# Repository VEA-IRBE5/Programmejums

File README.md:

# Programmējums
Zondes borta datora (mikrokontroliera) programmējums

# Programmēšanas stila vadlīnijas
Šīs ir tikai vadlīnijas, nesitīšu ja perfekti nesekosiet tām. Galvenais, lai kods ir saprotams un pārskatāms
- Tabulācija ir 4 atstarpes
- Komentārus var latviski/english, galvenais lai ir saprotami un labi apraksta kodu
- Iesaku komentārus netaupīt, tiklīdz kaut kas liekas ne pilnīgi pašsaprotams, raksti komentāru
- Komentāru garumam nevajadzētu pārsniegt 2 - 3 līnijas

## Mainīgo noformējums

- Mainīgo nosaukums var būt īsi līdz vidēji tekstuāls, galvenais lai no nosaukuma ir aptuveni skaidrs, kur izmanto
- Visim mainīgiem ir jābūt definētiem vienā vietā (vai divās) un, kur nepieiciešams, ar komentāriem aprakstīts to pielietojums
- Šīs pašas vadlīnijas arī attiecas uz definētām konstantēm
- Lūgums turēt mainīgos ārpus header (main.h) faila, cik iespējams (Uz konstantēm tas neattiecas)

## Koda noformējums

- Galvenā doma ir sadalīšana pa blokiem ar attiecīgām komentētām sadalēm
- Piemērā ir redzams ADC pārtraukums kā galvenais bloks, ar iekšējiem darbības soļiem sadalītiem mazākos blokos
- Var dalīt kodu pa blokiem arī pēc saviem ieskatiem, galvenais lai ir labi sadalīts

## #include un funkcijas

- Pie #include droši rakstiet komentārus
- Funkcijām lūdzu veidot aprakstu, pasakot ko dara, ko ievada (ar mainīgo aprakstu) un ko izvada
- Ja izmantojat gatavus koda blokus no citiem avotiem, tos iesaku turēt atsevišķos failos un integrēt kā funkcijas

# Git bash konfigurācija un lokālās repozitorijas izveide

### 1. Instalē git bash

### 2. Izveido mapi, kurā glabās projektu

### 3. R-click(otrais peles taustiņš) -> Git bash here
  - Ja nerāda, atver git bash un ar cd navigē uz izveidoto mapi

### 4. Konsolē: git config --global user.name "Vards Uzvards" 
- git config --global user.email "epasts@mail.com"
  - Izmanto to epastu, kurš piesaistīts profilam, kas var tikt klāt IRBE5 repozitorijai
  - Var pārbaudīt, vai pareizi saglabāts ar tām pašām komandām, noņemot "" specificētos datus

### 5. (Neobligāts)Konsolē: git config --global core.editor "'C:/Program Files/Notepad++/notepad++.exe' -multiInst -notabbar -nosession -noPlugin"
  - var uzstādīt notepad++ kā default teksta editoru, kad raksta commit komentāru
  - Iesaku izdarīt, jo konsoles teksta editors nav ērts

### 6. Konsolē: git config --global init.defaultBranch main
- Citādi defaults būs master, un tas var radīt problēmas

### 7. Konsolē: git config --list
- Ar šo var pārbaudīt git bash konfigurāciju

### 8. Beidzot inicializē lokālo repozitoriju: git init

# Darbība ar lokālo github repositoriju

### 1. Konsolē: git remote add IRBE5 https://github.com/VEA-IRBE5/Programmejums.git
- turpmāk pie git pull var izmantot IRBE5 nevis pilno linku 
- ar šo pastās, vai sarakstā ir Konsolē: git remote -v

### 2. Konsolē: git pull IRBE5 [Branch name]
- Lejupielādē norādītā zara saturu no repozitorijas, par zaru lietošanu konsultējies ar nodaļas galveno

### 3. Pēc pašreizējās darba tūres beigšanas neaizmirsti izveidot commit, lai dati nepazūd
- Konsolē: git add . (vai git add "filename", ja negrib visas izmaiņas pievienot)
- Konsolē: git status (pastās, vai viss ir ok)
- Konsolē: git commit (Lūdzu izsmeļoši un ne pārāk gari aprakstiet izmainīto)(var izmantot: -m "Text here")
   
### 4. Kad liekas, ka pašreizējais uzdevums ir gana labā stāvoklī, Konsolē: git push IRBE5 [Branch name]

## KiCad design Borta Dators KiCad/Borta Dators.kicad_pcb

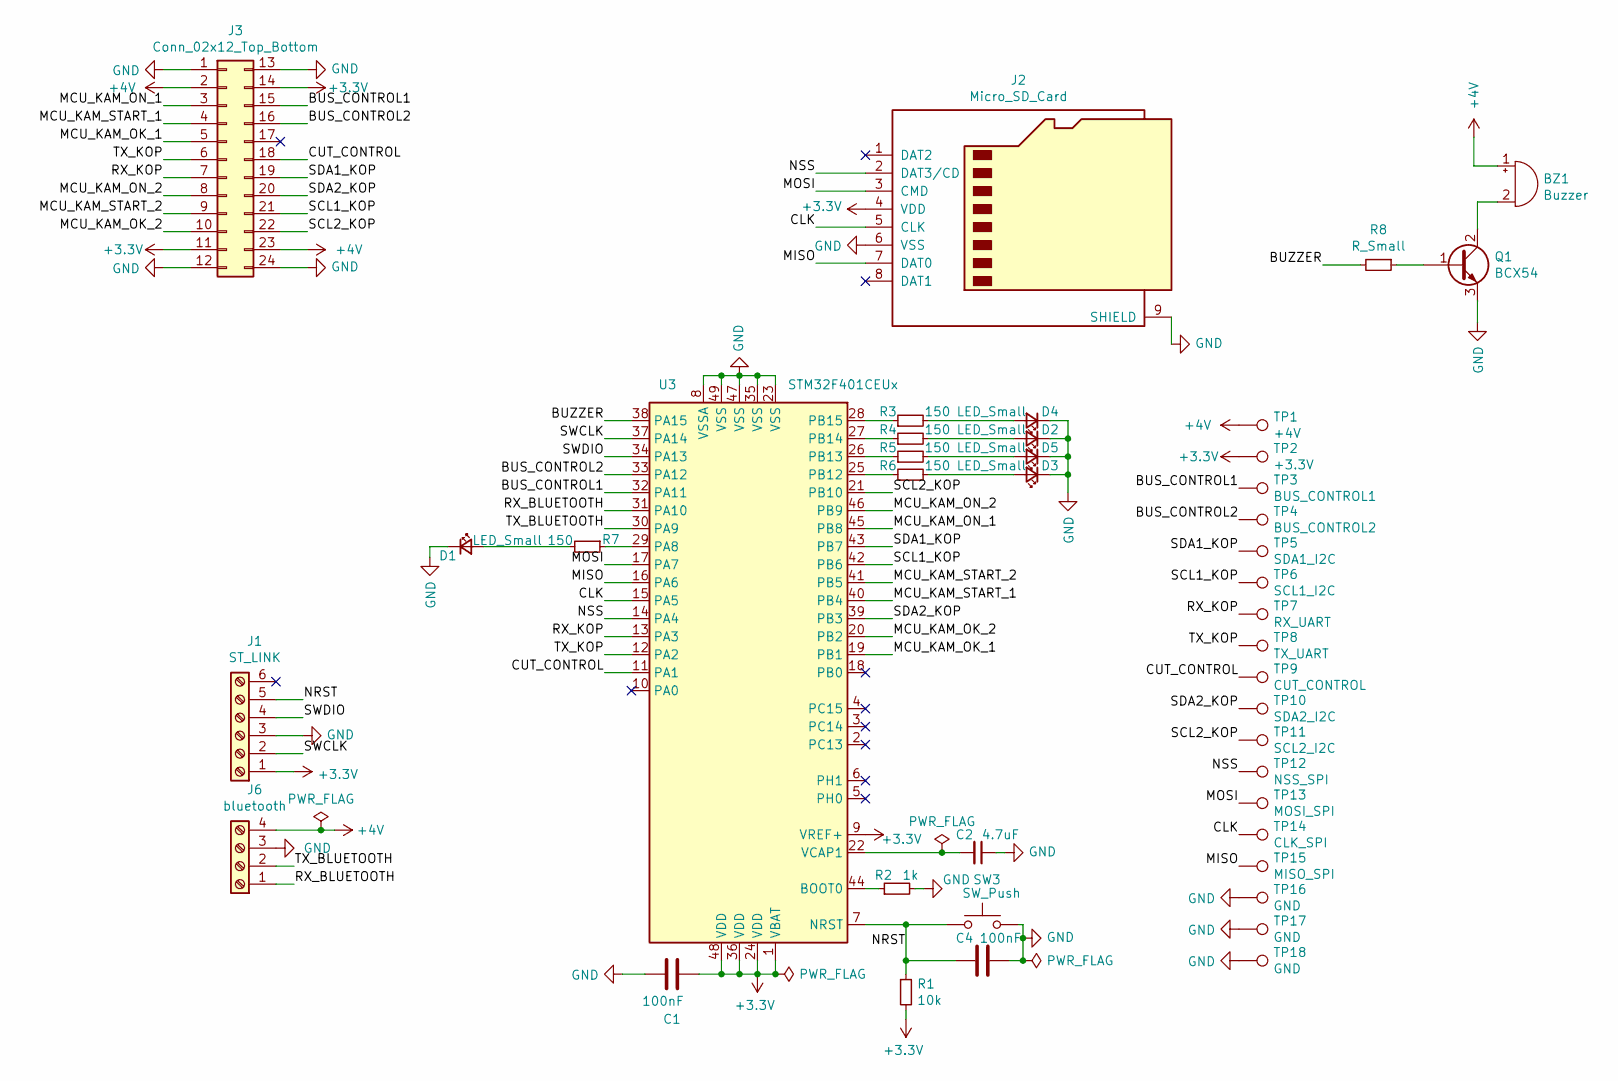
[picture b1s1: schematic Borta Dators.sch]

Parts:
BZ1: Buzzer; PinHeader_1x02_P1.27mm_Vertical
C1, C4: 100nF; C_0603_1608Metric_Pad1.08x0.95mm_HandSolder
C2: 4.7uF; C_0603_1608Metric_Pad1.08x0.95mm_HandSolder
D1, D2, D3, D4, D5: LED_Small; D_0603_1608Metric_Pad1.05x0.95mm_HandSolder
J1: ST_LINK; PinSocket_1x06_P2.54mm_Vertical
J2: Micro_SD_Card; Micro_SD
J3: Conn_02x12_Top_Bottom; SAMTEC-SSW-112-02-X-D-RA
J6: bluetooth; PinSocket_1x04_P2.54mm_Vertical
Q1: BCX54; SOT-89-3
R1: 10k; R_0603_1608Metric_Pad0.98x0.95mm_HandSolder
R2: 1k; R_0603_1608Metric_Pad0.98x0.95mm_HandSolder
R3, R4, R5, R6, R7: 150; R_0603_1608Metric_Pad0.98x0.95mm_HandSolder
R8: R_Small; R_0603_1608Metric_Pad0.98x0.95mm_HandSolder
SW3: SW_Push; SW_SPST_EVQQ2
TP1: +4V; PinHeader_1x01_P2.54mm_Vertical
TP2: +3.3V; PinHeader_1x01_P2.54mm_Vertical
TP3: BUS_CONTROL1; PinHeader_1x01_P2.54mm_Vertical
TP4: BUS_CONTROL2; PinHeader_1x01_P2.54mm_Vertical
TP5: SDA1_I2C; PinHeader_1x01_P2.54mm_Vertical
TP6: SCL1_I2C; PinHeader_1x01_P2.54mm_Vertical
TP7: RX_UART; PinHeader_1x01_P2.54mm_Vertical
TP8: TX_UART; PinHeader_1x01_P2.54mm_Vertical
TP9: CUT_CONTROL; PinHeader_1x01_P2.54mm_Vertical
TP10: SDA2_I2C; PinHeader_1x01_P2.54mm_Vertical
TP11: SCL2_I2C; PinHeader_1x01_P2.54mm_Vertical
TP12: NSS_SPI; PinHeader_1x01_P2.54mm_Vertical
TP13: MOSI_SPI; PinHeader_1x01_P2.54mm_Vertical
TP14: CLK_SPI; PinHeader_1x01_P2.54mm_Vertical
TP15: MISO_SPI; PinHeader_1x01_P2.54mm_Vertical
TP16, TP17, TP18: GND; PinHeader_1x01_P2.54mm_Vertical
U3: STM32F401CEUx; QFN-48-1EP_7x7mm_P0.5mm_EP5.6x5.6mm

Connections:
+3V3: C1.1, J1.1, J2.4 (VDD), J3.11, J3.14, R1.2, TP2.1, U3.1 (VBAT), U3.9 (VREF+), U3.24 (VDD), U3.36 (VDD), U3.48 (VDD); also elsewhere on the board
+4V: BZ1.1 (-), J3.2, J3.23, J6.4, TP1.1
/BUS_CONTROL1: J3.15, TP3.1, U3.32 (PA11); also elsewhere on the board
/BUS_CONTROL2: J3.16, TP4.1, U3.33 (PA12); also elsewhere on the board
/BUZZER: R8.2, U3.38 (PA15); also elsewhere on the board
/CLK: J2.5 (CLK), TP14.1, U3.15 (PA5); also elsewhere on the board
/CUT_CONTROL: J3.18, TP9.1, U3.11 (PA1); also elsewhere on the board
/MCU_KAM_OK_1: J3.5, U3.19 (PB1); also elsewhere on the board
/MCU_KAM_OK_2: J3.10, U3.20 (PB2); also elsewhere on the board
/MCU_KAM_ON_1: J3.3, U3.45 (PB8); also elsewhere on the board
/MCU_KAM_ON_2: J3.8, U3.46 (PB9); also elsewhere on the board
/MCU_KAM_START_1: J3.4, U3.40 (PB4); also elsewhere on the board
/MCU_KAM_START_2: J3.9, U3.41 (PB5); also elsewhere on the board
/MISO: J2.7 (DAT0), TP15.1, U3.16 (PA6); also elsewhere on the board
/MOSI: J2.3 (CMD), TP13.1, U3.17 (PA7); also elsewhere on the board
/NRST: C4.1, J1.5, R1.1, SW3.1, U3.7 (NRST); also elsewhere on the board
/NSS: J2.2 (DAT3/CD), TP12.1, U3.14 (PA4); also elsewhere on the board
/RX_BLUETOOTH: J6.1, U3.31 (PA10); also elsewhere on the board
/RX_KOP: J3.7, TP7.1, U3.13 (PA3); also elsewhere on the board
/SCL1_KOP: J3.21, TP6.1, U3.42 (PB6); also elsewhere on the board
/SCL2_KOP: J3.22, TP11.1, U3.21 (PB10); also elsewhere on the board
/SDA1_KOP: J3.19, TP5.1, U3.43 (PB7); also elsewhere on the board
/SDA2_KOP: J3.20, TP10.1, U3.39 (PB3); also elsewhere on the board
/SWCLK: J1.2, U3.37 (PA14); also elsewhere on the board
/SWDIO: J1.4, U3.34 (PA13); also elsewhere on the board
/TX_BLUETOOTH: J6.2, U3.30 (PA9); also elsewhere on the board
/TX_KOP: J3.6, TP8.1, U3.12 (PA2); also elsewhere on the board
GND: C1.2, C2.1, C4.2, D1.1 (K), D2.1 (K), D3.1 (K), D4.1 (K), D5.1 (K), J1.3, J2.6 (VSS), J2.9 (SHIELD), J3.1, J3.12, J3.13, J3.24, J6.3, Q1.3 (E), R2.2, SW3.2, TP16.1, TP17.1, TP18.1, U3.8 (VSSA), U3.23 (VSS), U3.35 (VSS), U3.47 (VSS), U3.49 (VSS); also elsewhere on the board
unnamed: BZ1.2 (+), Q1.2 (C)
unnamed 29: C2.2, U3.22 (VCAP1); also elsewhere on the board
unnamed: D1.2 (A), R7.2
unnamed: D2.2 (A), R4.2
unnamed: D3.2 (A), R6.2
unnamed: D4.2 (A), R3.2
unnamed: D5.2 (A), R5.2
unnamed: Q1.1 (B), R8.1
unnamed 40: R2.1, U3.44 (BOOT0); also elsewhere on the board
unnamed 41: R3.1, U3.28 (PB15); also elsewhere on the board
unnamed 42: R4.1, U3.27 (PB14); also elsewhere on the board
unnamed 43: R5.1, U3.26 (PB13); also elsewhere on the board
unnamed 44: R6.1, U3.25 (PB12); also elsewhere on the board
unnamed 45: R7.1, U3.29 (PA8); also elsewhere on the board

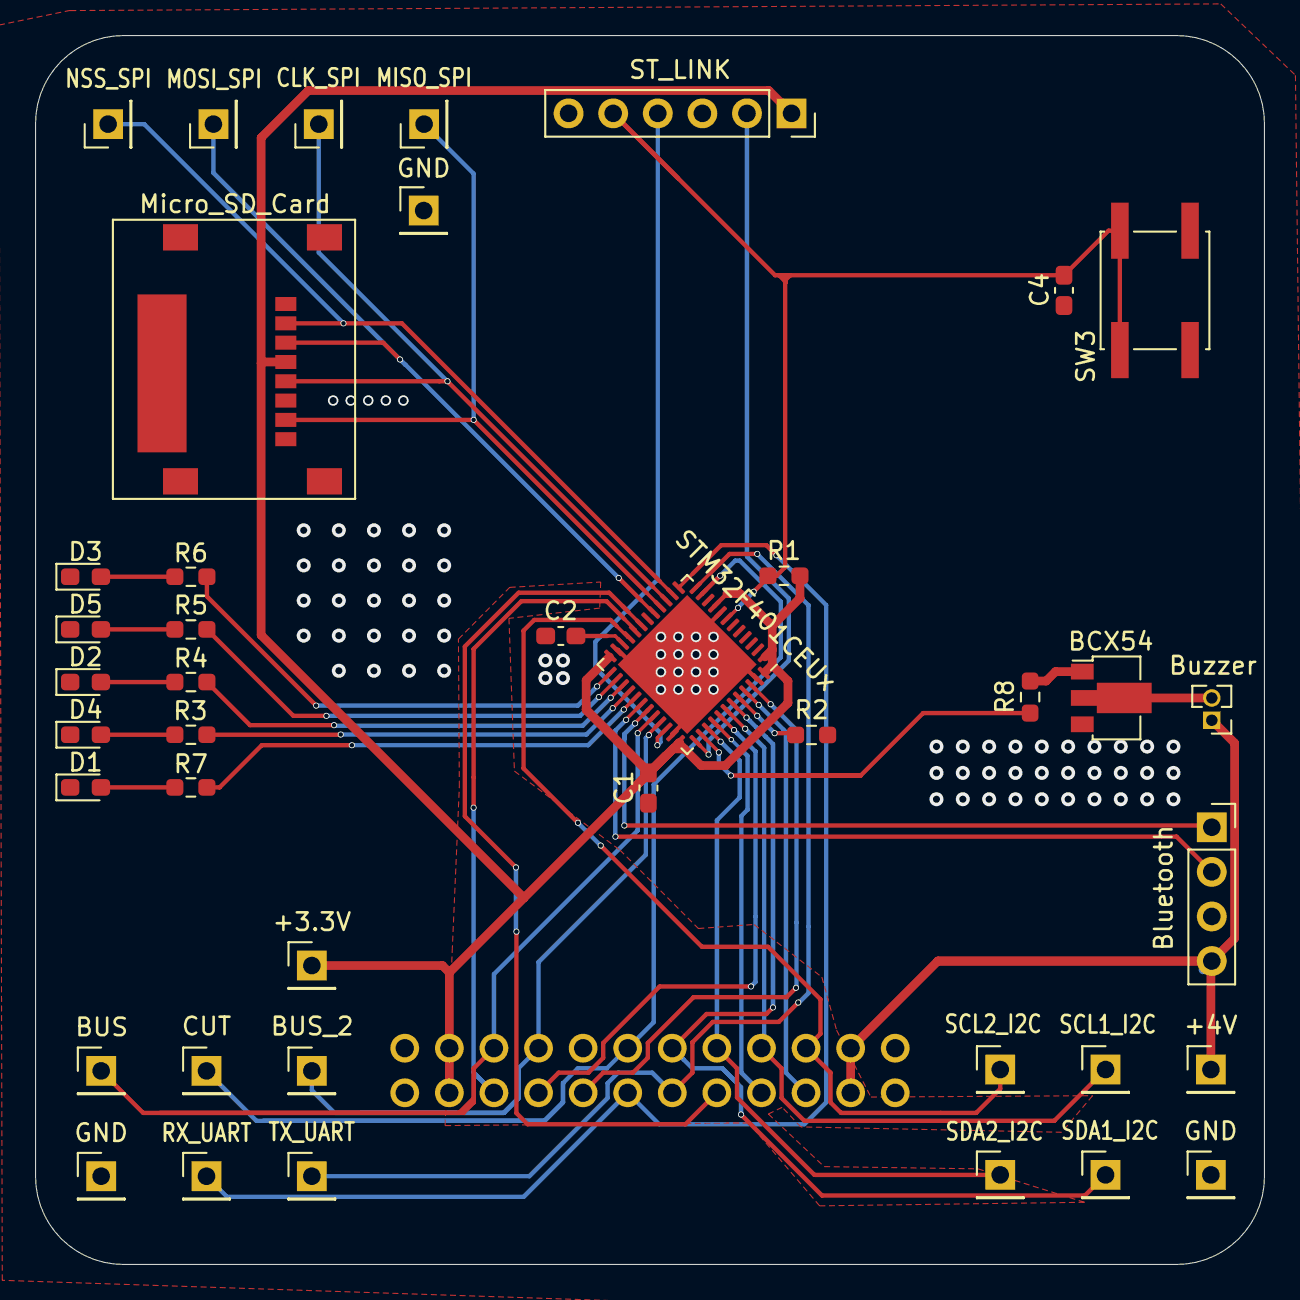
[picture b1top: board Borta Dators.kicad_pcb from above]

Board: 2 copper layers, 70.0 x 70.0 mm, 42 parts (0 on the bottom side), 42 nets.

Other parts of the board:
TP109: BUS_2; PinHeader_1x01_P2.54mm_Vertical
Ue: STM32F401CEUx; QFN-48-1EP_7x7mm_P0.5mm_EP5.6x5.6mm

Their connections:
+3V3: Ue.1, Ue.9, Ue.24, Ue.36, Ue.48; also elsewhere on the board
/BUS_CONTROL1: Ue.32; also elsewhere on the board
/BUS_CONTROL2: TP109.1, Ue.33; also elsewhere on the board
/BUZZER: Ue.38; also elsewhere on the board
/CLK: Ue.15; also elsewhere on the board
/CUT_CONTROL: Ue.11; also elsewhere on the board
/MCU_KAM_OK_1: Ue.19; also elsewhere on the board
/MCU_KAM_OK_2: Ue.20; also elsewhere on the board
/MCU_KAM_ON_1: Ue.45; also elsewhere on the board
/MCU_KAM_ON_2: Ue.46; also elsewhere on the board
/MCU_KAM_START_1: Ue.40; also elsewhere on the board
/MCU_KAM_START_2: Ue.41; also elsewhere on the board
/MISO: Ue.16; also elsewhere on the board
/MOSI: Ue.17; also elsewhere on the board
/NRST: Ue.7; also elsewhere on the board
/NSS: Ue.14; also elsewhere on the board
/RX_BLUETOOTH: Ue.31; also elsewhere on the board
/RX_KOP: Ue.13; also elsewhere on the board
/SCL1_KOP: Ue.42; also elsewhere on the board
/SCL2_KOP: Ue.21; also elsewhere on the board
/SDA1_KOP: Ue.43; also elsewhere on the board
/SDA2_KOP: Ue.39; also elsewhere on the board
/SWCLK: Ue.37; also elsewhere on the board
/SWDIO: Ue.34; also elsewhere on the board
/TX_BLUETOOTH: Ue.30; also elsewhere on the board
/TX_KOP: Ue.12; also elsewhere on the board
GND: Ue.8, Ue.23, Ue.35, Ue.47, Ue.49; also elsewhere on the board
unnamed 29: Ue.22; also elsewhere on the board
unnamed 40: Ue.44; also elsewhere on the board
unnamed 41: Ue.28; also elsewhere on the board
unnamed 42: Ue.27; also elsewhere on the board
unnamed 43: Ue.26; also elsewhere on the board
unnamed 44: Ue.25; also elsewhere on the board
unnamed 45: Ue.29; also elsewhere on the board

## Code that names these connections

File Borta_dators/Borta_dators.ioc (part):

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Mcu.Name=STM32F401C(D-E)Ux
Mcu.Package=UFQFPN48
Mcu.UserName=STM32F401CEUx
PA1.GPIOParameters=GPIO_Label
PA1.GPIO_Label=ROPE_CUT_EN
PA1.Signal=GPIO_Output
PA10.Mode=Asynchronous
PA10.Signal=USART1_RX
PA11.GPIOParameters=PinState,GPIO_Label
PA11.GPIO_Label=BUS_SEL_1
PA11.PinState=GPIO_PIN_SET
PA11.Signal=GPIO_Output
PA12.GPIOParameters=PinState,GPIO_Label
PA12.GPIO_Label=BUS_SEL_2
PA12.PinState=GPIO_PIN_SET
PA12.Signal=GPIO_Output
PA13.Mode=Serial_Wire
PA13.Signal=SYS_JTMS-SWDIO
PA14.Mode=Serial_Wire
PA14.Signal=SYS_JTCK-SWCLK
PA15.GPIOParameters=GPIO_PuPd,GPIO_Label
PA15.GPIO_Label=BUZZER
PA15.GPIO_PuPd=GPIO_PULLDOWN
PA15.Signal=GPIO_Output
PA2.Mode=Asynchronous
PA2.Signal=USART2_TX
PA3.Mode=Asynchronous
PA3.Signal=USART2_RX
PA4.GPIOParameters=GPIO_Label
PA4.GPIO_Label=SD_CS
PA4.Signal=GPIO_Output
PA5.Mode=Full_Duplex_Master
PA5.Signal=SPI1_SCK
PA6.Mode=Full_Duplex_Master
PA6.Signal=SPI1_MISO
PA7.Mode=Full_Duplex_Master
PA7.Signal=SPI1_MOSI
PA8.GPIOParameters=GPIO_Label
PA8.GPIO_Label=USER_LED1
PA8.Signal=GPIO_Output
PA9.Mode=Asynchronous
PA9.Signal=USART1_TX
PB1.GPIOParameters=PinState,GPIO_PuPd,GPIO_Label,GPIO_ModeDefaultOutputPP
PB1.GPIO_Label=CAM2_OK
PB1.GPIO_ModeDefaultOutputPP=GPIO_MODE_OUTPUT_OD
PB1.GPIO_PuPd=GPIO_NOPULL
PB1.PinState=GPIO_PIN_SET
PB1.Signal=GPIO_Output
PB10.Mode=I2C
PB10.Signal=I2C2_SCL
PB12.GPIOParameters=GPIO_Label
PB12.GPIO_Label=USER_LED3
PB12.Signal=GPIO_Output
PB13.GPIOParameters=GPIO_Label
PB13.GPIO_Label=USER_LED5
PB13.Signal=GPIO_Output
PB14.GPIOParameters=GPIO_Label
PB14.GPIO_Label=USER_LED2
PB14.Signal=GPIO_Output
PB15.GPIOParameters=GPIO_Label
PB15.GPIO_Label=USER_LED4
PB15.Signal=GPIO_Output
PB2.GPIOParameters=PinState,GPIO_PuPd,GPIO_Label,GPIO_ModeDefaultOutputPP
PB2.GPIO_Label=CAM1_OK
PB2.GPIO_ModeDefaultOutputPP=GPIO_MODE_OUTPUT_OD
PB2.GPIO_PuPd=GPIO_NOPULL
PB2.PinState=GPIO_PIN_SET
PB2.Signal=GPIO_Output
PB3.Mode=I2C
PB3.Signal=I2C2_SDA
PB4.GPIOParameters=GPIO_PuPd,GPIO_Label,GPIO_ModeDefaultEXTI
PB4.GPIO_Label=CAM2_START
PB4.GPIO_ModeDefaultEXTI=GPIO_MODE_IT_FALLING
PB4.GPIO_PuPd=GPIO_PULLUP
PB4.Signal=GPXTI4
PB5.GPIOParameters=GPIO_PuPd,GPIO_Label,GPIO_ModeDefaultEXTI
PB5.GPIO_Label=CAM1_START
PB5.GPIO_ModeDefaultEXTI=GPIO_MODE_IT_FALLING
PB5.GPIO_PuPd=GPIO_PULLUP
PB5.Signal=GPXTI5
PB6.Mode=I2C
PB6.Signal=I2C1_SCL
PB7.Mode=I2C
PB7.Signal=I2C1_SDA
PB8.GPIOParameters=GPIO_Label
PB8.GPIO_Label=CAM2_ON
PB8.Signal=GPIO_Output
PB9.GPIOParameters=GPIO_Label
PB9.GPIO_Label=CAM1_ON
PB9.Signal=GPIO_Output
RCC.HSE_VALUE=25000000
RCC.SYSCLKFreq_VALUE=16000000
board=custom

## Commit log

2021-09-20 README v1
2021-09-20 Koda piemēru augšupielāde
2021-09-20 README papilinājums ar vadlīnijām
2021-09-20 Failu reorganizācija
2021-09-20 README korekcijas
2021-09-20 README korekcija 3
2021-09-20 README uzlabojums
2022-04-22 File import
2022-04-22 Local file upload to hub
2022-05-22 checksum implementation for communication with COM mcu
2022-05-22 Telemetry string has first comma (',') removed
2022-05-22 Misc stuff update
2022-05-24 Checksum correction and UART2 receiver automatic reset after a few seconds of inactivity
2022-05-27 Implemented sensor reinitialisation functionality in case of short term sensor failure and added altitude data filtering logic
2022-06-28 [FIX some issues]
2022-07-05 [MCU<->COM]
    - Pārtraukumu apstrādes procedūrā optimizācijas dēļ mainīgajiem tika piešķirtas konstantas vērtības [buffer size], kas mūsu risinājumā neder, jo buffera izmērs mainās.
